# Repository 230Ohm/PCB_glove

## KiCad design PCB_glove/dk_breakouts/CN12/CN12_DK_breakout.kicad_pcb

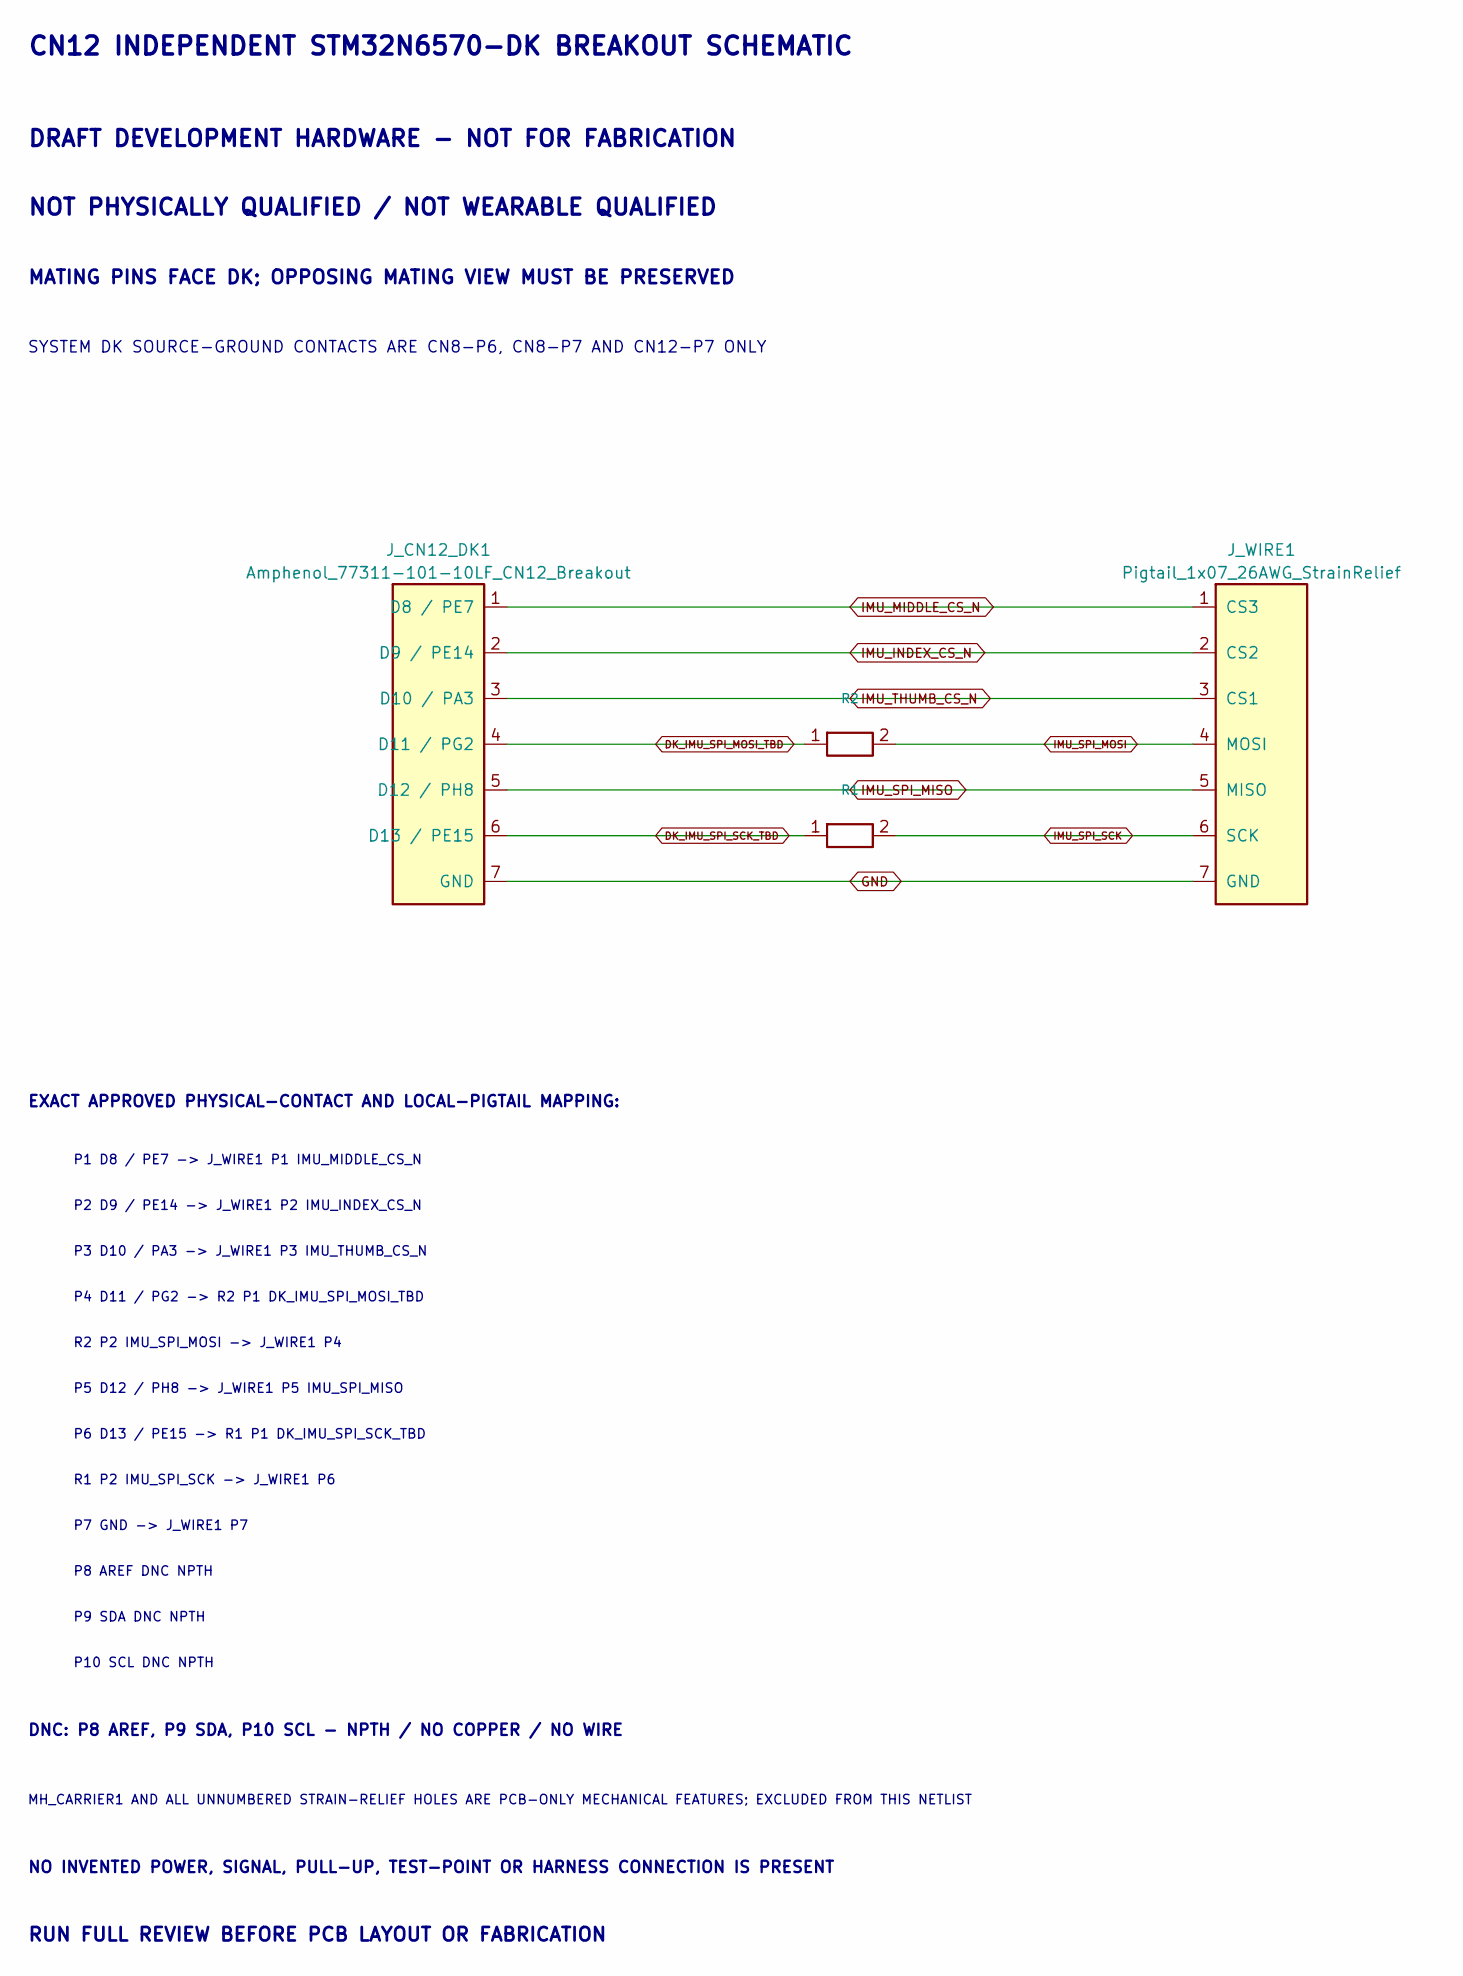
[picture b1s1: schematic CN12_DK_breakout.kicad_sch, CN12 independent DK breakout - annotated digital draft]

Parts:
J_CN12_DK1: Amphenol_77311-101-10LF_CN12_Breakout; MPN 77311-101-10LF
J_WIRE1: Pigtail_1x07_26AWG_StrainRelief; MPN TBD / NOT A PRODUCTION CONNECTOR
R1, R2: 0R/DNP/TBD_SERIES_OPTION; DRAFT_0R_Jumper_0603_VERIFY

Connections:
DK_IMU_SPI_MOSI_TBD: J_CN12_DK1.4 (D11 / PG2), R2.1
DK_IMU_SPI_SCK_TBD: J_CN12_DK1.6 (D13 / PE15), R1.1
GND: J_CN12_DK1.7 (GND), J_WIRE1.7 (GND)
IMU_INDEX_CS_N: J_CN12_DK1.2 (D9 / PE14), J_WIRE1.2 (CS2)
IMU_MIDDLE_CS_N: J_CN12_DK1.1 (D8 / PE7), J_WIRE1.1 (CS3)
IMU_SPI_MISO: J_CN12_DK1.5 (D12 / PH8), J_WIRE1.5 (MISO)
IMU_SPI_MOSI: J_WIRE1.4 (MOSI), R2.2
IMU_SPI_SCK: J_WIRE1.6 (SCK), R1.2
IMU_THUMB_CS_N: J_CN12_DK1.3 (D10 / PA3), J_WIRE1.3 (CS1)

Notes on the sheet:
CN12 INDEPENDENT STM32N6570-DK BREAKOUT SCHEMATIC
DRAFT DEVELOPMENT HARDWARE - NOT FOR FABRICATION
NOT PHYSICALLY QUALIFIED / NOT WEARABLE QUALIFIED
MATING PINS FACE DK; OPPOSING MATING VIEW MUST BE PRESERVED
SYSTEM DK SOURCE-GROUND CONTACTS ARE CN8-P6, CN8-P7 AND CN12-P7 ONLY
EXACT APPROVED PHYSICAL-CONTACT AND LOCAL-PIGTAIL MAPPING:
P1 D8 / PE7 -> J_WIRE1 P1 IMU_MIDDLE_CS_N
P2 D9 / PE14 -> J_WIRE1 P2 IMU_INDEX_CS_N
P3 D10 / PA3 -> J_WIRE1 P3 IMU_THUMB_CS_N
P4 D11 / PG2 -> R2 P1 DK_IMU_SPI_MOSI_TBD
R2 P2 IMU_SPI_MOSI -> J_WIRE1 P4
P5 D12 / PH8 -> J_WIRE1 P5 IMU_SPI_MISO
P6 D13 / PE15 -> R1 P1 DK_IMU_SPI_SCK_TBD
R1 P2 IMU_SPI_SCK -> J_WIRE1 P6
P7 GND -> J_WIRE1 P7
P8 AREF DNC NPTH
P9 SDA DNC NPTH
P10 SCL DNC NPTH
DNC: P8 AREF, P9 SDA, P10 SCL - NPTH / NO COPPER / NO WIRE
MH_CARRIER1 AND ALL UNNUMBERED STRAIN-RELIEF HOLES ARE PCB-ONLY MECHANICAL FEATURES; EXCLUDED FROM THIS NETLIST
NO INVENTED POWER, SIGNAL, PULL-UP, TEST-POINT OR HARNESS CONNECTION IS PRESENT
RUN FULL REVIEW BEFORE PCB LAYOUT OR FABRICATION

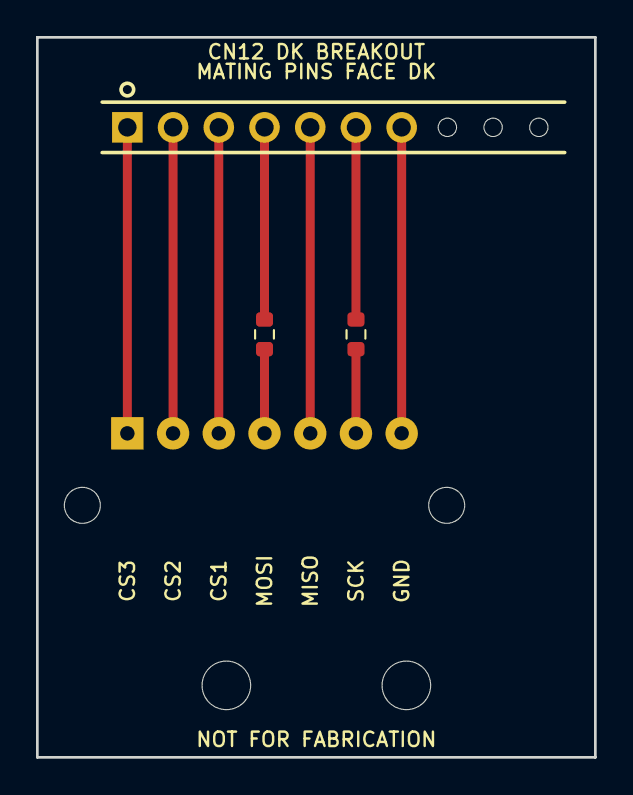
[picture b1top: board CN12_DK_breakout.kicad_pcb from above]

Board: 2 copper layers, 31.0 x 40.0 mm, 5 parts (0 on the bottom side), 9 nets.

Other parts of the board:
MH_CARRIER1: CARRIER_CLAMP_MECHANICAL_VERIFY; Carrier_Clamp_2x_M2.5_NPTH_P10mm

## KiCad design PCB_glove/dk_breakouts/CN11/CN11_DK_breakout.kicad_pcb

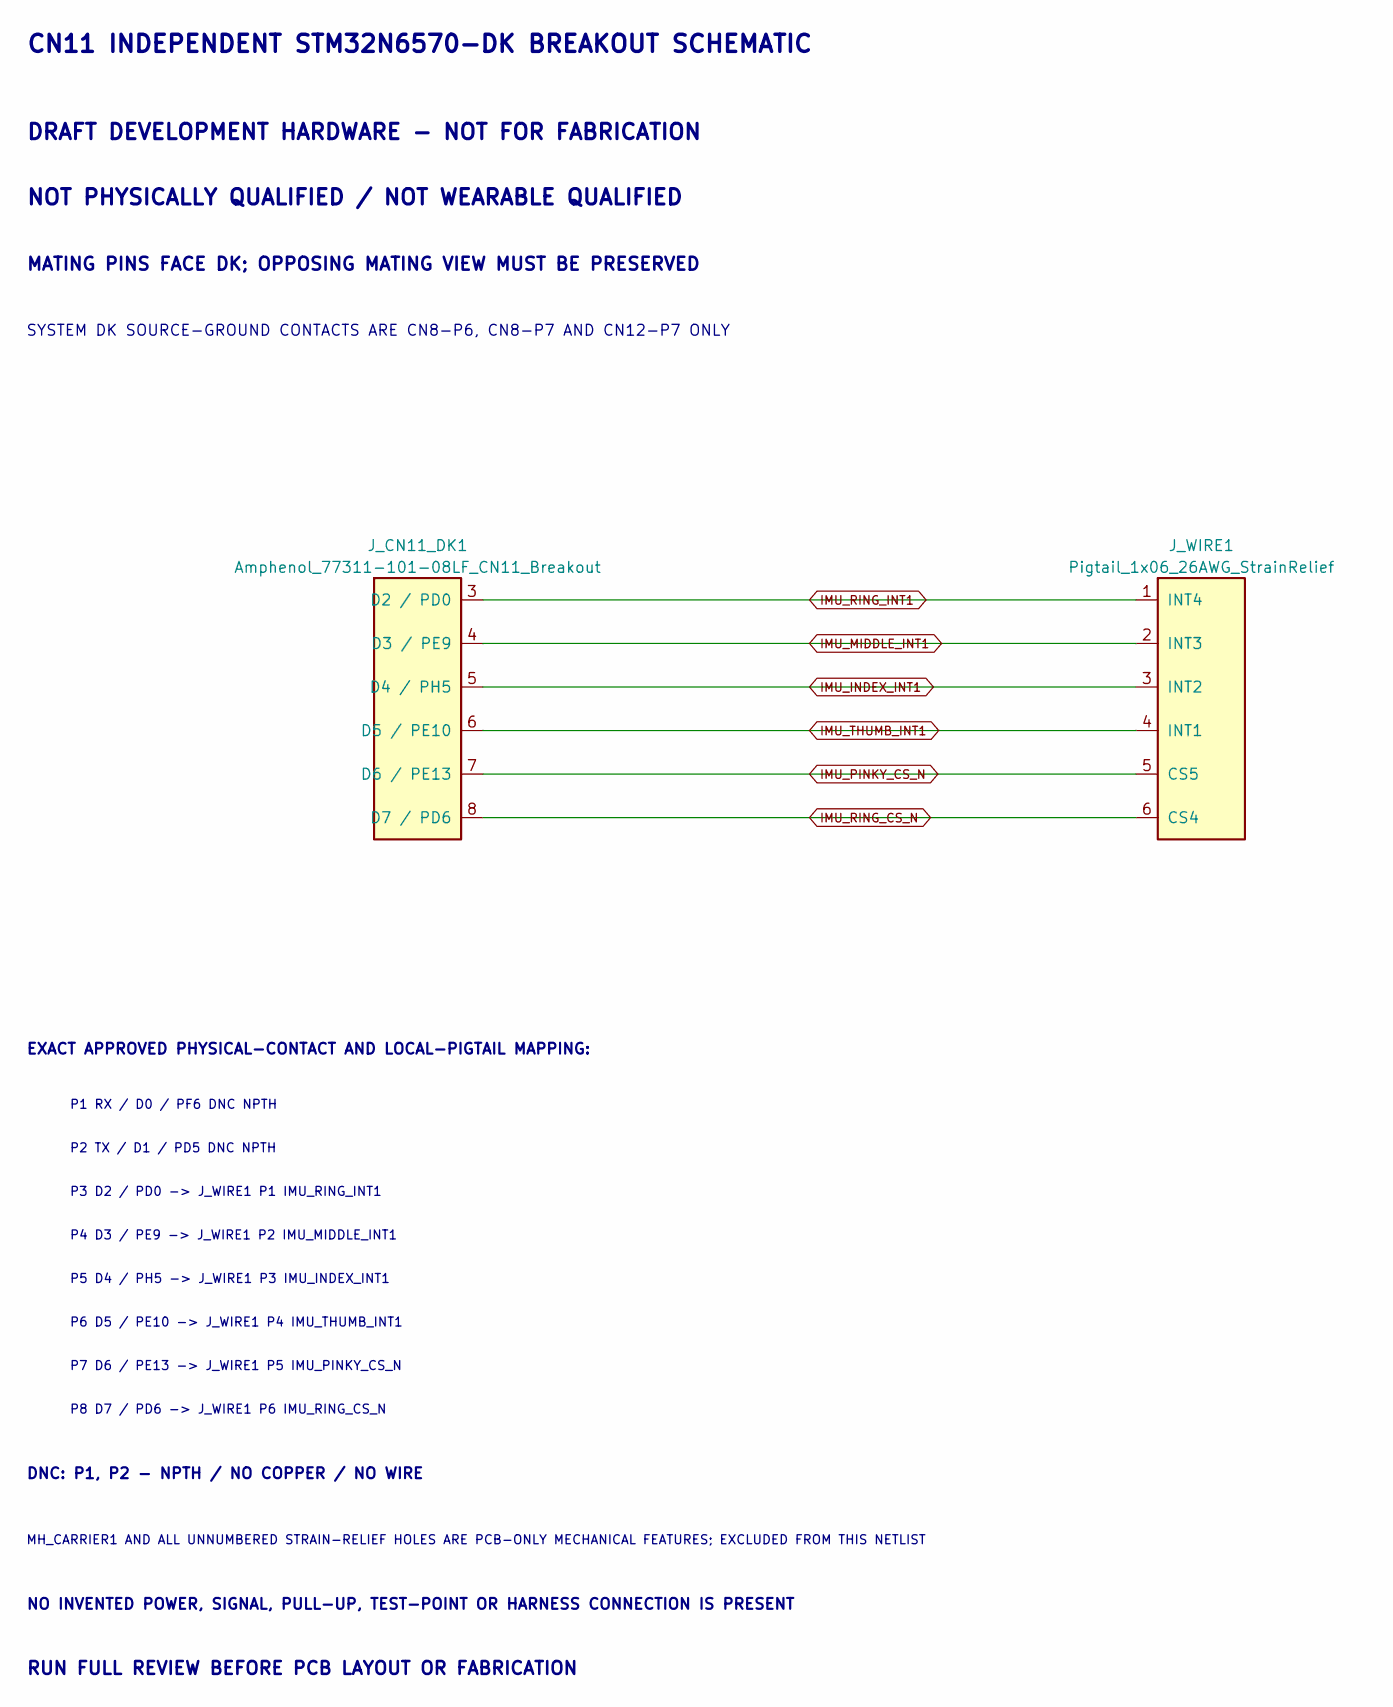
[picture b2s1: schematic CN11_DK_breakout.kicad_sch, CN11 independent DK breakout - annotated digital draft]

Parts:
J_CN11_DK1: Amphenol_77311-101-08LF_CN11_Breakout; MPN 77311-101-08LF
J_WIRE1: Pigtail_1x06_26AWG_StrainRelief; MPN TBD / NOT A PRODUCTION CONNECTOR

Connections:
IMU_INDEX_INT1: J_CN11_DK1.5 (D4 / PH5), J_WIRE1.3 (INT2)
IMU_MIDDLE_INT1: J_CN11_DK1.4 (D3 / PE9), J_WIRE1.2 (INT3)
IMU_PINKY_CS_N: J_CN11_DK1.7 (D6 / PE13), J_WIRE1.5 (CS5)
IMU_RING_CS_N: J_CN11_DK1.8 (D7 / PD6), J_WIRE1.6 (CS4)
IMU_RING_INT1: J_CN11_DK1.3 (D2 / PD0), J_WIRE1.1 (INT4)
IMU_THUMB_INT1: J_CN11_DK1.6 (D5 / PE10), J_WIRE1.4 (INT1)

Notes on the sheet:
CN11 INDEPENDENT STM32N6570-DK BREAKOUT SCHEMATIC
DRAFT DEVELOPMENT HARDWARE - NOT FOR FABRICATION
NOT PHYSICALLY QUALIFIED / NOT WEARABLE QUALIFIED
MATING PINS FACE DK; OPPOSING MATING VIEW MUST BE PRESERVED
SYSTEM DK SOURCE-GROUND CONTACTS ARE CN8-P6, CN8-P7 AND CN12-P7 ONLY
EXACT APPROVED PHYSICAL-CONTACT AND LOCAL-PIGTAIL MAPPING:
P1 RX / D0 / PF6 DNC NPTH
P2 TX / D1 / PD5 DNC NPTH
P3 D2 / PD0 -> J_WIRE1 P1 IMU_RING_INT1
P4 D3 / PE9 -> J_WIRE1 P2 IMU_MIDDLE_INT1
P5 D4 / PH5 -> J_WIRE1 P3 IMU_INDEX_INT1
P6 D5 / PE10 -> J_WIRE1 P4 IMU_THUMB_INT1
P7 D6 / PE13 -> J_WIRE1 P5 IMU_PINKY_CS_N
P8 D7 / PD6 -> J_WIRE1 P6 IMU_RING_CS_N
DNC: P1, P2 - NPTH / NO COPPER / NO WIRE
MH_CARRIER1 AND ALL UNNUMBERED STRAIN-RELIEF HOLES ARE PCB-ONLY MECHANICAL FEATURES; EXCLUDED FROM THIS NETLIST
NO INVENTED POWER, SIGNAL, PULL-UP, TEST-POINT OR HARNESS CONNECTION IS PRESENT
RUN FULL REVIEW BEFORE PCB LAYOUT OR FABRICATION

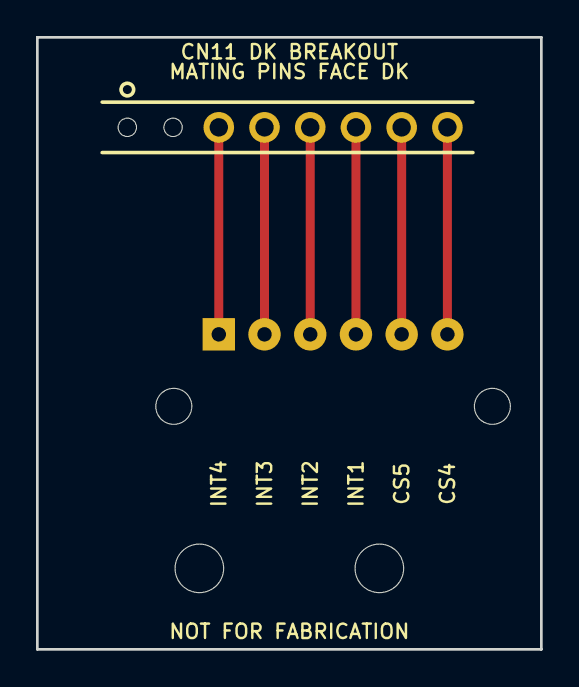
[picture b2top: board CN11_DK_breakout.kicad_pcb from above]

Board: 2 copper layers, 28.0 x 34.0 mm, 3 parts (0 on the bottom side), 6 nets.

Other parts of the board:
MH_CARRIER1: CARRIER_CLAMP_MECHANICAL_VERIFY; Carrier_Clamp_2x_M2.5_NPTH_P10mm

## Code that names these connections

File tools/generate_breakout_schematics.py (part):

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        dk_mpn="77311-101-08LF",
        dk_footprint="Amphenol_77311-101-08LF_CN11_Breakout",
        dk_pins=(
            Pin("3", "D2 / PD0", "IMU_RING_INT1"),
            Pin("4", "D3 / PE9", "IMU_MIDDLE_INT1"),
            Pin("5", "D4 / PH5", "IMU_INDEX_INT1"),
            Pin("6", "D5 / PE10", "IMU_THUMB_INT1"),
            Pin("7", "D6 / PE13", "IMU_PINKY_CS_N"),
            Pin("8", "D7 / PD6", "IMU_RING_CS_N"),
        ),
        pigtail_footprint="Pigtail_1x06_26AWG_StrainRelief",
        pigtail_pins=(
            Pin("1", "INT4", "IMU_RING_INT1"),
            Pin("2", "INT3", "IMU_MIDDLE_INT1"),
            Pin("3", "INT2", "IMU_INDEX_INT1"),
            Pin("4", "INT1", "IMU_THUMB_INT1"),
            Pin("5", "CS5", "IMU_PINKY_CS_N"),
            Pin("6", "CS4", "IMU_RING_CS_N"),
        ),
        physical_contacts=(
            "P1 RX / D0 / PF6 DNC NPTH",
            "P2 TX / D1 / PD5 DNC NPTH",
            "P3 D2 / PD0 -> J_WIRE1 P1 IMU_RING_INT1",
            "P4 D3 / PE9 -> J_WIRE1 P2 IMU_MIDDLE_INT1",
            "P5 D4 / PH5 -> J_WIRE1 P3 IMU_INDEX_INT1",
            "P6 D5 / PE10 -> J_WIRE1 P4 IMU_THUMB_INT1",
            "P7 D6 / PE13 -> J_WIRE1 P5 IMU_PINKY_CS_N",
            "P8 D7 / PD6 -> J_WIRE1 P6 IMU_RING_CS_N",
        ),
        dnc_summary="DNC: P1, P2 - NPTH / NO COPPER / NO WIRE",
    ),
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        dk_mpn="77311-101-10LF",
        dk_footprint="Amphenol_77311-101-10LF_CN12_Breakout",
        dk_pins=(
            Pin("1", "D8 / PE7", "IMU_MIDDLE_CS_N"),
            Pin("2", "D9 / PE14", "IMU_INDEX_CS_N"),
            Pin("3", "D10 / PA3", "IMU_THUMB_CS_N"),
            Pin("4", "D11 / PG2", "DK_IMU_SPI_MOSI_TBD"),
            Pin("5", "D12 / PH8", "IMU_SPI_MISO"),
            Pin("6", "D13 / PE15", "DK_IMU_SPI_SCK_TBD"),
            Pin("7", "GND", "GND"),
        ),
        pigtail_footprint="Pigtail_1x07_26AWG_StrainRelief",
        pigtail_pins=(
            Pin("1", "CS3", "IMU_MIDDLE_CS_N"),
            Pin("2", "CS2", "IMU_INDEX_CS_N"),
            Pin("3", "CS1", "IMU_THUMB_CS_N"),
            Pin("4", "MOSI", "IMU_SPI_MOSI"),
            Pin("5", "MISO", "IMU_SPI_MISO"),
            Pin("6", "SCK", "IMU_SPI_SCK"),
            Pin("7", "GND", "GND"),
        ),
        physical_contacts=(
            "P1 D8 / PE7 -> J_WIRE1 P1 IMU_MIDDLE_CS_N",
            "P2 D9 / PE14 -> J_WIRE1 P2 IMU_INDEX_CS_N",
            "P3 D10 / PA3 -> J_WIRE1 P3 IMU_THUMB_CS_N",
            "P4 D11 / PG2 -> R2 P1 DK_IMU_SPI_MOSI_TBD",
            "R2 P2 IMU_SPI_MOSI -> J_WIRE1 P4",
            "P5 D12 / PH8 -> J_WIRE1 P5 IMU_SPI_MISO",
            "P6 D13 / PE15 -> R1 P1 DK_IMU_SPI_SCK_TBD",
            "R1 P2 IMU_SPI_SCK -> J_WIRE1 P6",
            "P7 GND -> J_WIRE1 P7",
            "P8 AREF DNC NPTH",
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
